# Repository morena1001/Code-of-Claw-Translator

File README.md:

# Code-of-Claw-Translator
The Code of Claw is a fictional system of communication in the series "Gregor the Overlander", and uses a combination of clicks, scratches, and tap to represent letters and other characters. The point of this project is to capture those inputs, analyze them, and return English characters.

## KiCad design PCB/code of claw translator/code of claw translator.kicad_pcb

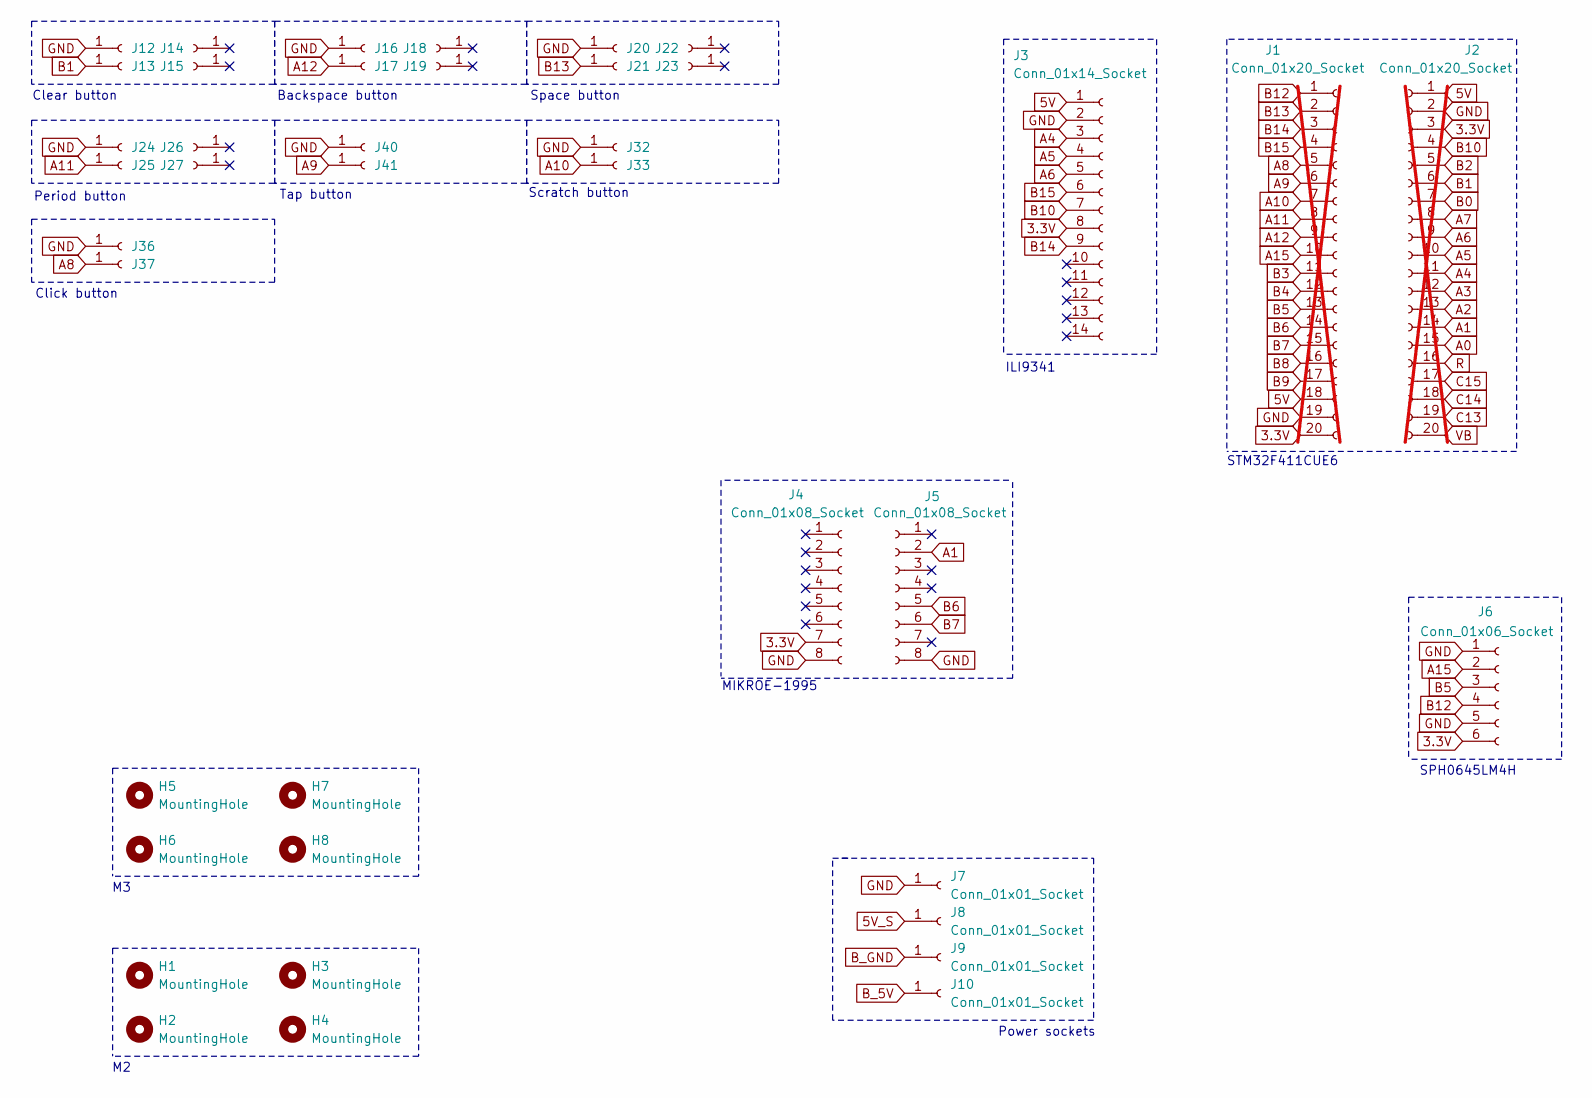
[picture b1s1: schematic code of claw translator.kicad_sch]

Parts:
H1, H2, H3, H4: MountingHole; MountingHole_2.2mm_M2
H5, H6, H7, H8: MountingHole; MountingHole_3.2mm_M3
J1, J2: Conn_01x20_Socket; PinSocket_1x20_P2.54mm_Vertical; not fitted
J3: Conn_01x14_Socket; PinSocket_1x14_P2.54mm_Vertical
J4, J5: Conn_01x08_Socket; PinSocket_1x08_P2.54mm_Vertical
J6: Conn_01x06_Socket; PinSocket_1x06_P2.54mm_Vertical
J7, J8, J9, J10, J12, J13, J14, J15, J16, J17, J18, J19, J20, J21, J22, J23, J24, J25, J26, J27: Conn_01x01_Socket; PinSocket_1x01_P2.54mm_Vertical
J32, J33, J36, J37, J40, J41: Conn_01x01_Socket; PinSocket_1x01_P2.54mm_Horizontal

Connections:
3.3V: J1.20, J2.3, J3.8, J4.7, J6.6
5V: J1.18, J2.1, J3.1
5V_S: J8.1
A0: J2.15
A1: J2.14, J5.2
A2: J2.13
A3: J2.12
A4: J2.11, J3.3
A5: J2.10, J3.4
A6: J2.9, J3.5
A7: J2.8
A8: J1.5, J37.1
A9: J1.6, J41.1
A10: J1.7, J33.1
A11: J1.8, J25.1
A12: J1.9, J17.1
A15: J1.10, J6.2
B0: J2.7
B1: J2.6, J13.1
B2: J2.5
B3: J1.11
B4: J1.12
B5: J1.13, J6.3
B6: J1.14, J5.5
B7: J1.15, J5.6
B8: J1.16
B9: J1.17
B10: J2.4, J3.7
B12: J1.1, J6.4
B13: J1.2, J21.1
B14: J1.3, J3.9
B15: J1.4, J3.6
B_5V: J10.1
B_GND: J9.1
C13: J2.19
C14: J2.18
C15: J2.17
GND: J1.19, J2.2, J3.2, J4.8, J5.8, J6.1, J6.5, J7.1, J12.1, J16.1, J20.1, J24.1, J32.1, J36.1, J40.1
R: J2.16
VB: J2.20

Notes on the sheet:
Space button
Tap button
Backspace button
Period button
SPH0645LM4H
STM32F411CUE6
Power sockets
Clear button
ILI9341
Scratch button
Click button
MIKROE-1995

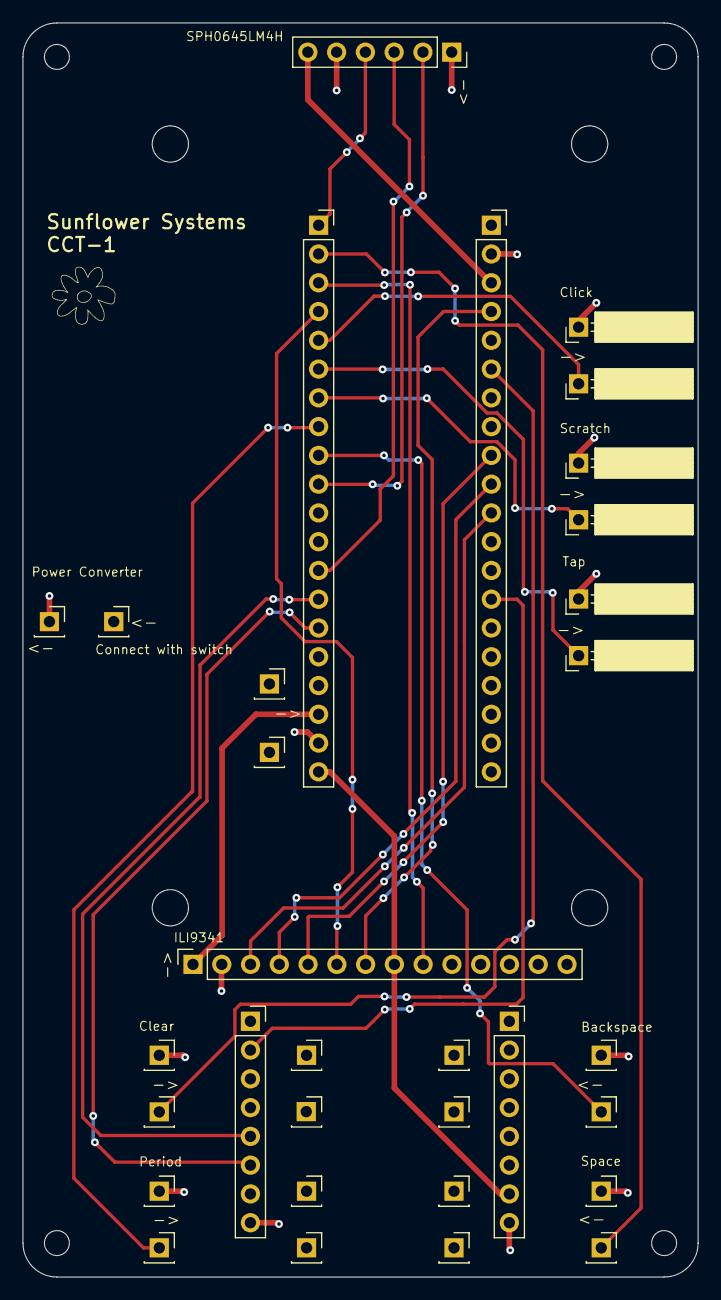
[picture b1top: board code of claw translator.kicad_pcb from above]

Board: 2 copper layers, 59.6 x 110.7 mm, 40 parts (0 on the bottom side), 22 nets.

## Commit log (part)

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2026-03-04 Finished the first version of the click recognizer using only amplitude. I will want to make tweaks to the sample size and the exponential equations for the sound envelope. Sometimesclicks don't get 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
2026-03-10 Began work on the driver for the ILI9341 IC present on the screen. Was able to get communication set up. Next is to finish init function and begin printing pixels.
2026-03-11 Made changes to the init function
2026-03-12 Figure out how to write a pixel, just need to test it.
2026-03-15 Can finally write pixels to the screen. Had to borrow init code from somewhere else because I didn't really check what commands I would need to set up the device. My job now is to figure out what eac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
2026-03-19 can finally print pixels. Next is characters
2026-03-22 Can finally print characters to the screen and fill screen. Need to find a fast screen fill algorithm. Need to also be able to delete characters, and format for multiple lines
2026-03-25 Need to test out the rest of the new functions.
2026-03-26 Finished testing all functions, and it seems to be working. I could test for the edge cases, but I will do that later. I can now start working on the touch screen capabilities
2026-03-30 Added project for touch controller.
2026-04-02 Can communicate with the touch controller. Now need to develop the code to differentiate between touches and taps
2026-04-13 Last commit of first version of tap and scratch driver
2026-04-14 Using trackpad module, I can now know when a tap or scratch has been performed. Now want to add interrupts to it
2026-04-14 Updated driver to work with interrupts. Will want to make the program respond to quicker inputs. Might need to reduce the idle period
2026-04-15 was able to make it respond faster, but discovered a quick to swiping. There needs to be a small stationary period before the start of the swipe or else the IC won't process it correctly. I will need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
2026-04-15 Mark design tasks as completed in Task Decomposition
2026-04-15 Added new configuration commands to initilization and I think it works ?
2026-04-17 Created the project file for the final simulation and began adding header files for the drivers. Will want to start first by adding helper functions to the LCD screen.
2026-04-18 Update task decomposition with completed buttons
    Updated task list to reflect completed buttons and features. Also removed the space button because it would have served the same functionality as the character confirm button.
2026-04-18 Combined the LCD screen with the helper buttons. Now need to add the trackpad and the microphone, as well as the helper functions for the microphone.
2026-04-19 Added code for the trackpad and developed a driver for it. Now need to plug in the trackpad, test it to see that it works, and clean up and document the other two drivers.
2026-04-20 Compiled and ran the new program. Need to debug it
2026-04-20 Trackpad worked first try. To make it faster however I think it will be worth using the other core available on this device. First have to check the blue pill has two cores too.
2026-04-23 Finished adding the code for the click envelope to the final simulation. Just need to test and debug it now.
2026-04-28 Working on new version of the click envelope function
2026-04-30 Second version, but it still doesn't work. I think I may have to also experiment with incoming frequencies. I may also look into AI that can recognize human clicks. I don't think my original amplitud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
2026-05-23 Can finally use the rfft algorithm, now need to hook it up the microphone for real time rfft
2026-05-31 Can finally read input from microphone and perform an rfft on it to get peak Hz. Now need to determine if a certain sample includes a click
2026-06-03 Can finally properly recognize clicks and filters noise, including voices. Cannot yet filter out thumps. I could try to check how many samples it takes to 'normalize' before to see if it the samples 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
2026-06-07 Beginning to combine all components together. Will want to rework recognition software later
2026-06-10 Can now click with all the other components. Updated the clear screen function to be smarter and faster.
2026-06-12 Updated screen to look nicer.
2026-06-16 Finished visual cue system. Would now like to set up project on blue pill to see if it works
2026-06-17 Started setting up the project files for the blue pill
2026-06-21 Black pill project file initial commit
2026-06-21 Ported final code from stm32f3 to stm32f4
2026-06-24 Began working on the PCB
2026-06-24 Extra files for PCB
2026-06-25 Designing rough draft of final look
2026-06-28 Test of ported code to black pill was successful. Will now work on PCB
